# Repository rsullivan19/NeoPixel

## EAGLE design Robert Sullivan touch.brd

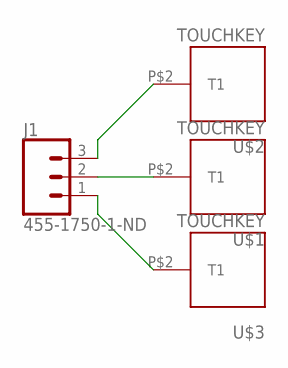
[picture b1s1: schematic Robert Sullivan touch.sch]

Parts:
J1: 455-1750-1-ND; 1X03
U$1, U$2, U$3: TOUCHKEY; TOUCHPAD

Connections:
unnamed: J1.3, U$2.P$2
unnamed: J1.1, U$3.P$2
unnamed: J1.2, U$1.P$2

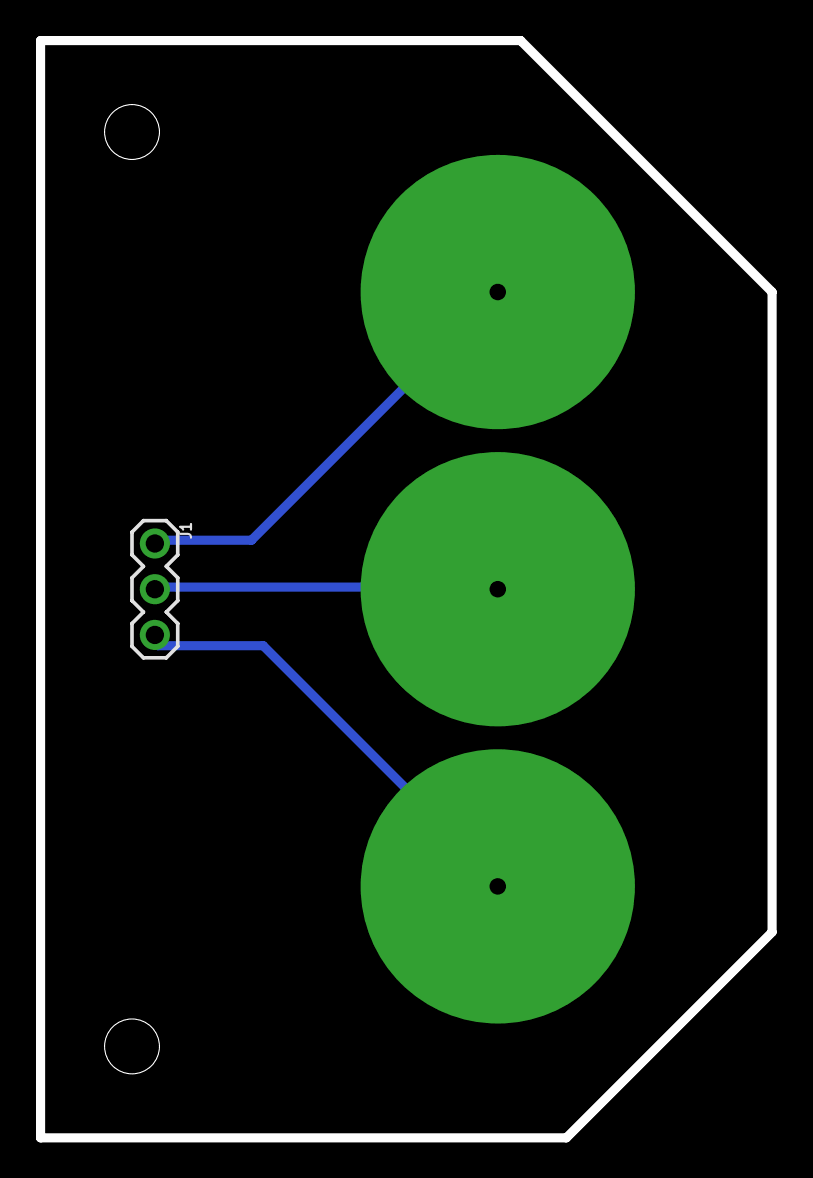
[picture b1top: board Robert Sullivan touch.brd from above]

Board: 2 copper layers, 40.6 x 61.0 mm, 4 parts (0 on the bottom side), 3 nets.

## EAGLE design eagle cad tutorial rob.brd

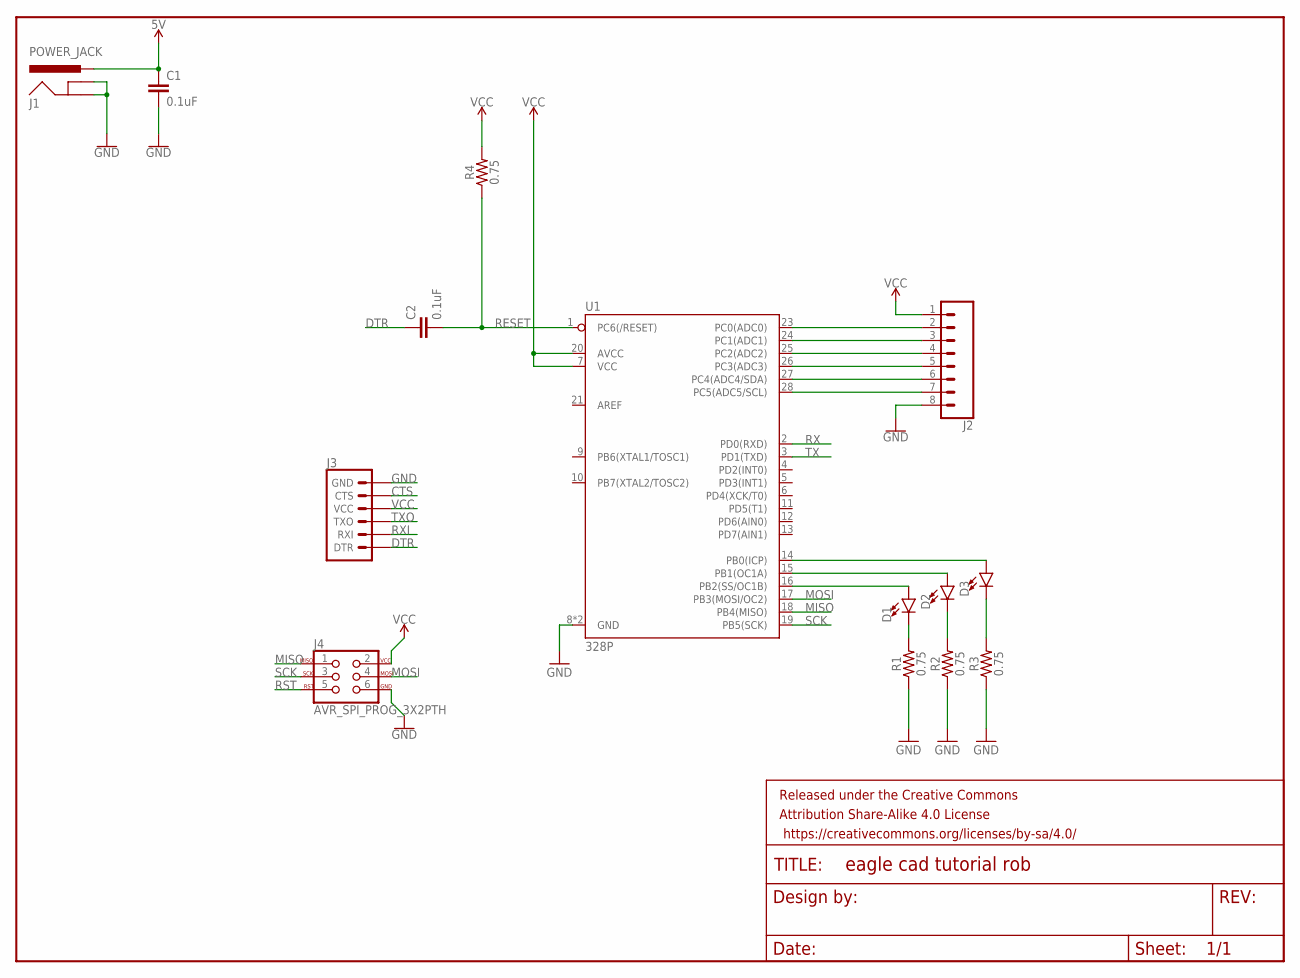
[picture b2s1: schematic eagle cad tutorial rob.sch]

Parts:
C1: 0.1uF; 0402
C2: 0.1uF; 0603
D1, D2, D3: LED5MM; LED_5MM
FRAME1: FRAME-LETTER; CREATIVE_COMMONS
J1: POWER_JACK; POWER_JACK_PTH
J2: CONN_08"; 1X08
J3: 6_PIN_SERIAL_TARGETSILK; 6_PIN_SERIAL_TARGET_SIDE_W_SILK
J4: AVR_SPI_PROG_3X2PTH; 2X3
R1, R2, R3, R4: 0.75; 0805
U1: 328P; DIP28

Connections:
5V: C1.1, J1.PWR
CTS: J3.P$5 (CTS)
DTR: C2.1, J3.P$1 (DTR)
GND: C1.2, J1.GND, J1.GNDBREAK, J2.8, J3.P$6 (GND), J4.6, R1.1, R2.1, R3.1, U1.8 (GND), U1.22 (GND)
MISO: J4.1, U1.18 (PB4(MISO))
MOSI: J4.4, U1.17 (PB3(MOSI/OC2))
unnamed: J2.2, U1.23 (PC0(ADC0))
unnamed: J2.3, U1.24 (PC1(ADC1))
unnamed: J2.4, U1.25 (PC2(ADC2))
unnamed: J2.5, U1.26 (PC3(ADC3))
unnamed: J2.6, U1.27 (PC4(ADC4/SDA))
unnamed: J2.7, U1.28 (PC5(ADC5/SCL))
unnamed: D1.A, U1.16 (PB2(SS/OC1B))
unnamed: D2.A, U1.15 (PB1(OC1A))
unnamed: D3.A, U1.14 (PB0(ICP))
unnamed: D3.K (C), R3.2
unnamed: D2.K (C), R2.2
unnamed: D1.K (C), R1.2
RESET: C2.2, R4.1, U1.1 (PC6(/RESET))
RST: J4.5
RX: U1.2 (PD0(RXD))
RXI: J3.P$3 (RXI)
SCK: J4.3, U1.19 (PB5(SCK))
TX: U1.3 (PD1(TXD))
TXO: J3.P$2 (TXO)
VCC: J2.1, J3.P$4 (VCC), J4.2, R4.2, U1.7 (VCC), U1.20 (AVCC)

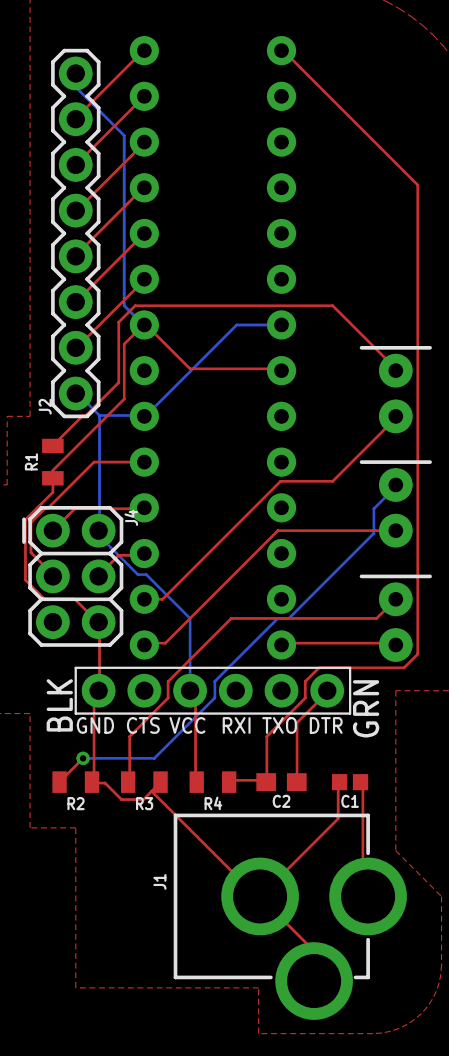
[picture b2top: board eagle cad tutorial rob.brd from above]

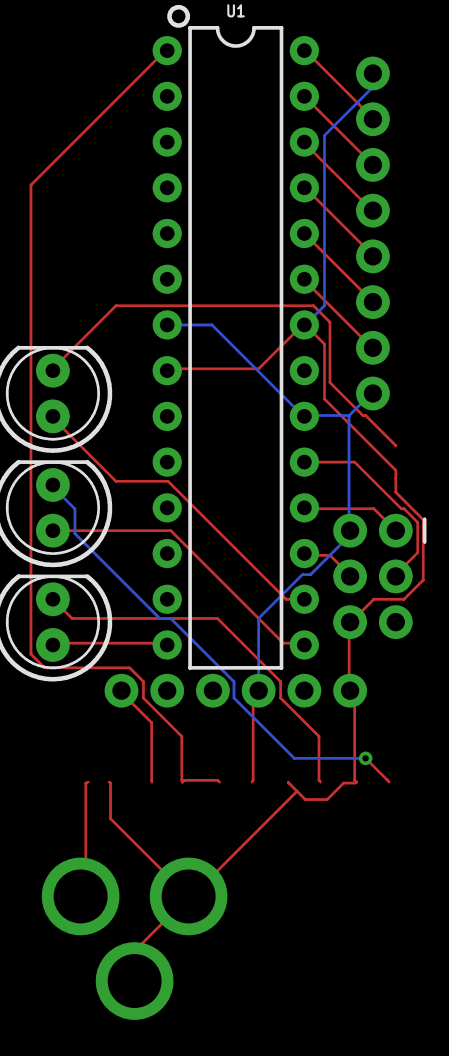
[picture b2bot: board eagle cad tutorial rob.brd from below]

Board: 2 copper layers, 15 parts (4 on the bottom side), 20 nets.

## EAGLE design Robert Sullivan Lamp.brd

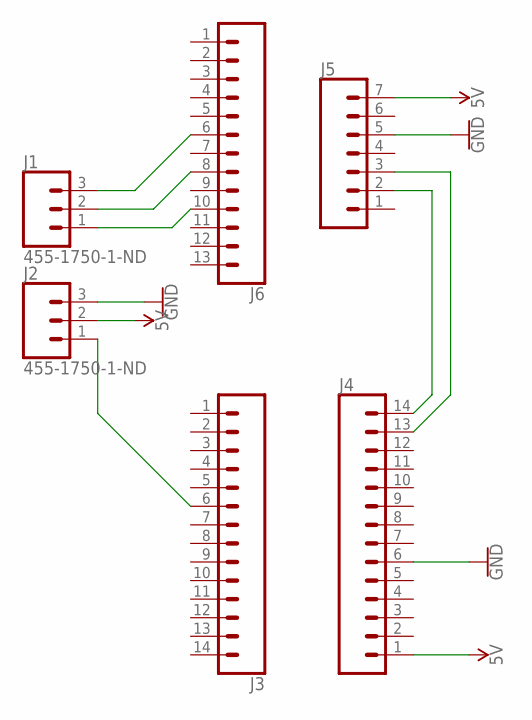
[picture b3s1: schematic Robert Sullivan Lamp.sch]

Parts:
J1, J2: 455-1750-1-ND; 1X03
J3, J4: CONN_14; 1X14
J5: CONN_07LOCK_LONGPADS; 1X07_LOCK_LONGPADS
J6: CONN_13; 1X13

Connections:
5V: J2.2, J4.1, J5.7
GND: J2.3, J4.6, J5.5
unnamed: J4.14, J5.2
unnamed: J4.13, J5.3
unnamed: J1.3, J6.6
unnamed: J1.2, J6.8
unnamed: J1.1, J6.10
unnamed: J2.1, J3.6

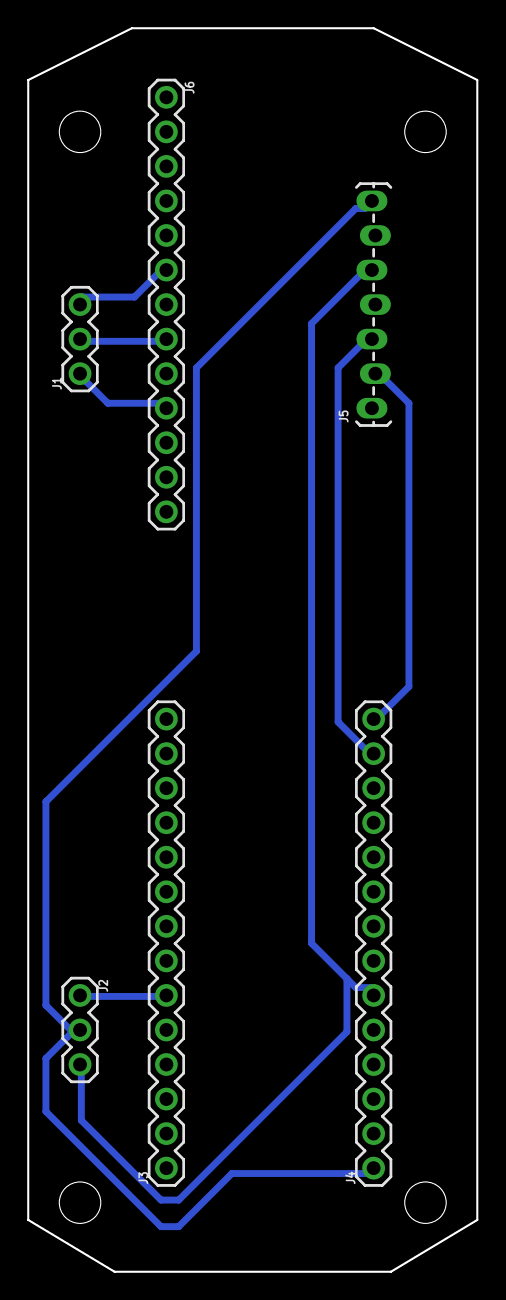
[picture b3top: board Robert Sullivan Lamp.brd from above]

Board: 2 copper layers, 33.0 x 91.4 mm, 6 parts (0 on the bottom side), 8 nets.

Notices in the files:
parts and their libraries:
SparkFun-Connectors: Licensing: Creative Commons ShareAlike 4.0 International - https://creativecommons.org/licenses/by-sa/4.0
SparkFun-Aesthetics: Released under the Creative Commons Attribution Share-Alike 4.0 License
SparkFun-Aesthetics: https://creativecommons.org/licenses/by-sa/4.0
